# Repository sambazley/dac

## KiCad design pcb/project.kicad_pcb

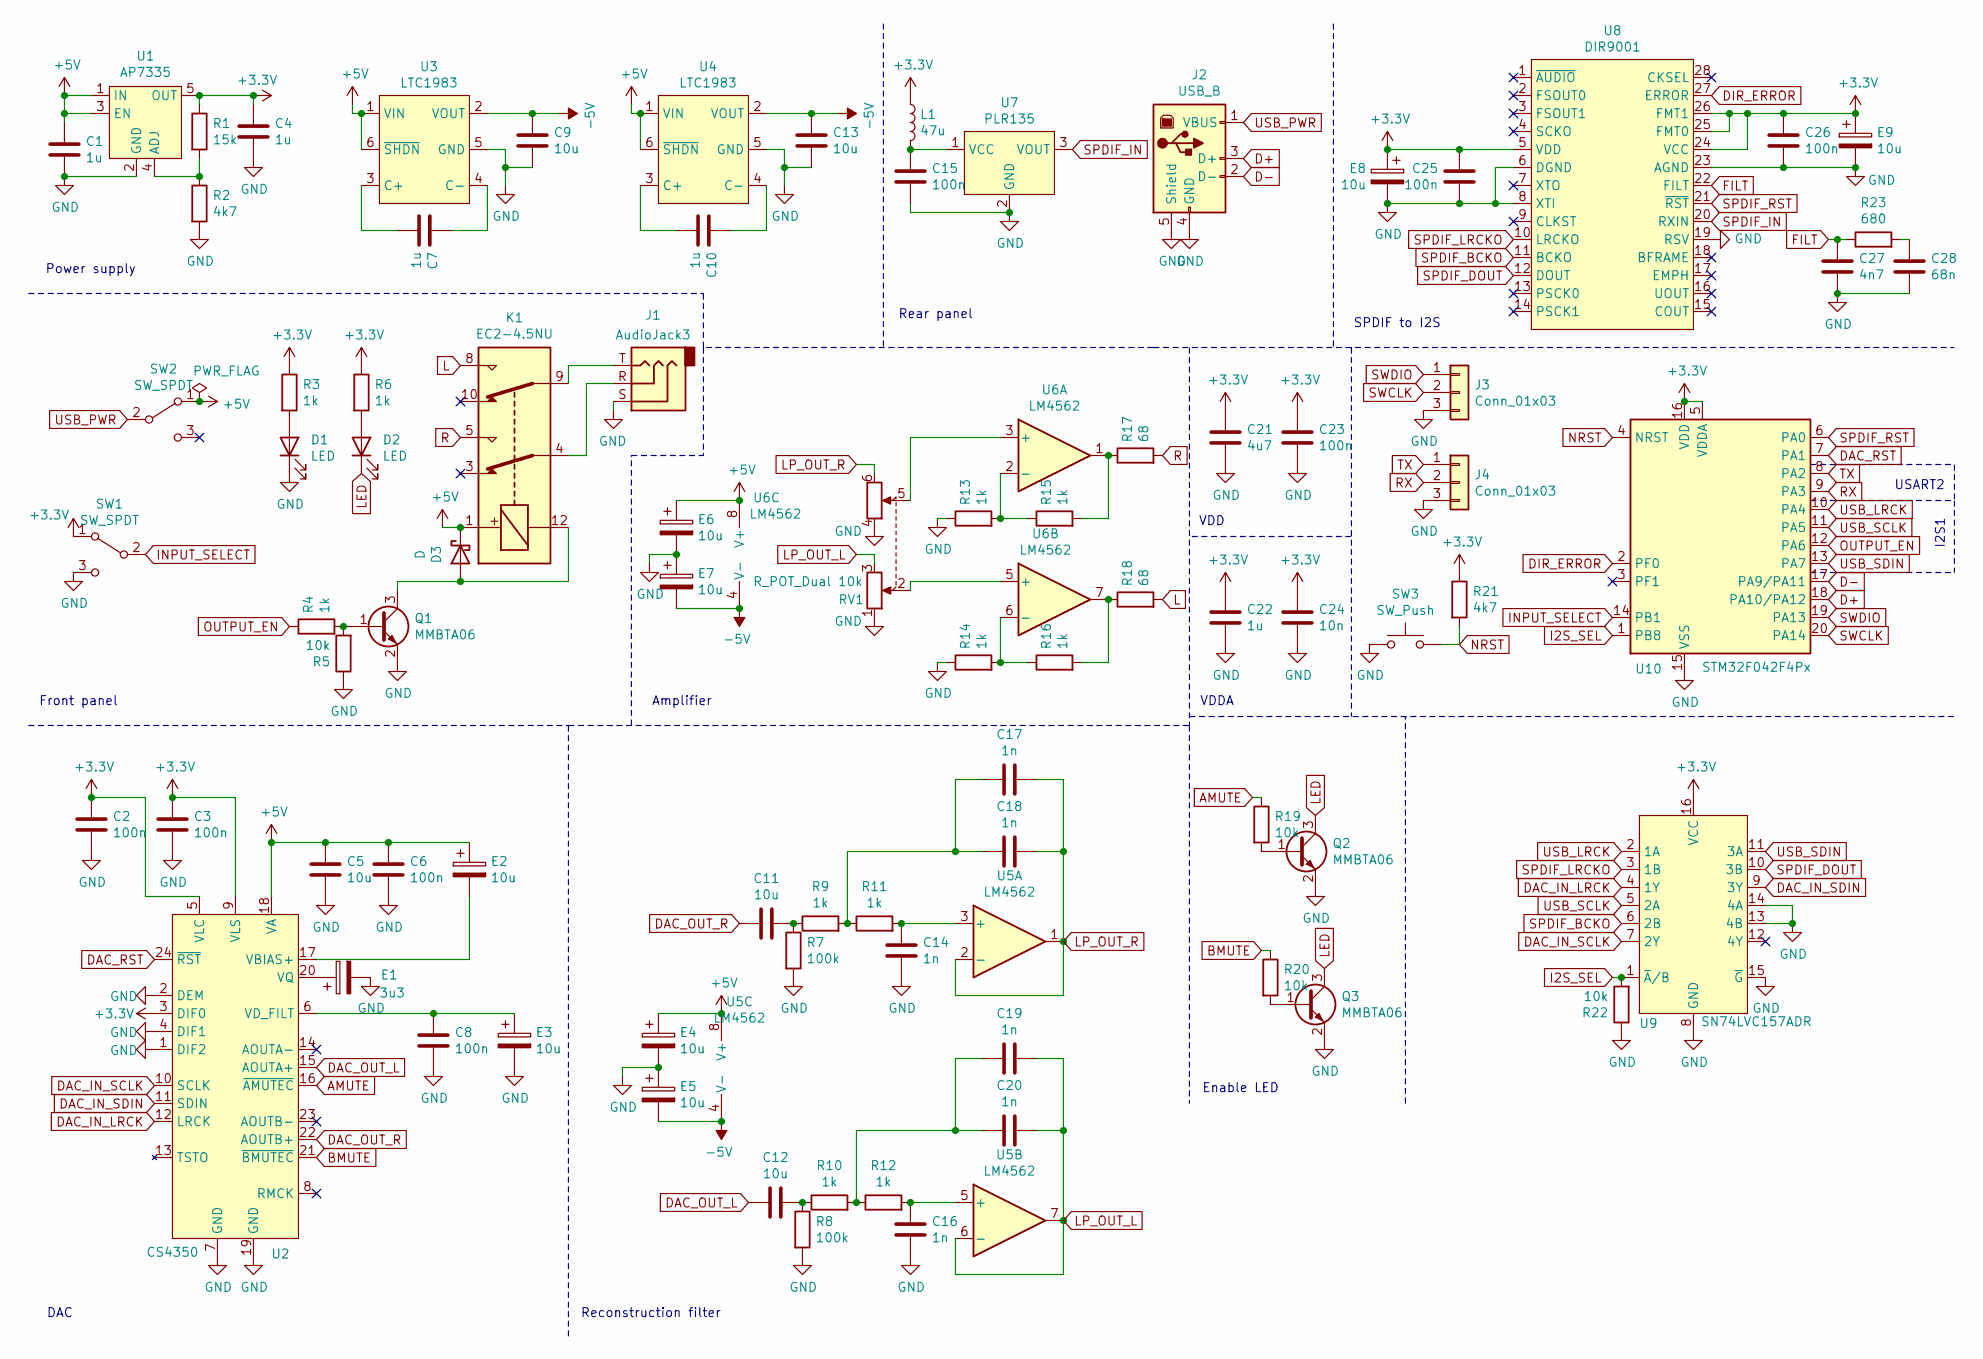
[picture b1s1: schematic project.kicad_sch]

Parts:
C1, C4, C7, C10, C22: 1u; C_0805_2012Metric
C2, C3, C6, C8, C15, C23, C25, C26: 100n; C_0805_2012Metric
C5, C9, C11, C12, C13: 10u; C_0805_2012Metric
C14, C16, C17, C18, C19, C20: 1n; C_0805_2012Metric
C21: 4u7; C_0805_2012Metric
C24: 10n; C_0805_2012Metric
C27: 4n7; C_0805_2012Metric
C28: 68n; C_0805_2012Metric
D1, D2: LED; LED_0805_2012Metric_Pad1.15x1.40mm_HandSolder
D3: D; D_SOD-523
E1: 3u3; CP_Elec_4x4.5
E2, E3, E4, E5, E6, E7, E8, E9: 10u; CP_Radial_D5.0mm_P2.00mm
J1: AudioJack3; SJ-63053A
J2: USB_B; UJ2-BH-TH
J3, J4: Conn_01x03; PinHeader_1x03_P2.54mm_Vertical
K1: EC2-4.5NU; Relay_DPDT_Kemet_EC2
L1: 47u; L_Taiyo-Yuden_NR-50xx
Q1, Q2, Q3: MMBTA06; SOT-23
R1: 15k; R_0805_2012Metric
R2, R21: 4k7; R_0805_2012Metric
R3, R4, R6, R9, R10, R11, R12, R13, R14, R15, R16: 1k; R_0805_2012Metric
R5, R19, R20, R22: 10k; R_0805_2012Metric
R7, R8: 100k; R_0805_2012Metric
R17, R18: 68; R_0805_2012Metric
R23: 680; R_0805_2012Metric
RV1: R_POT_Dual 10k; PTD902-2020K-A103
SW1, SW2: SW_SPDT; M2012SA2W40
SW3: SW_Push; SW_SPST_PTS645
U1: AP7335; SOT-23-5
U2: CS4350; TSSOP-24_4.4x7.8mm_P0.65mm
U3, U4: LTC1983; SOT-23-6
U5, U6: LM4562; DIP-8_W7.62mm_Socket
U7: PLR135
U8: DIR9001; TSSOP-28_4.4x9.7mm_P0.65mm
U9: ‎SN74LVC157ADR‎; SOIC-16_3.9x9.9mm_P1.27mm
U10: STM32F042F4Px; TSSOP-20_4.4x6.5mm_P0.65mm

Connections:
+3V3: C2.1, C3.1, C4.1, C21.1, C22.1, C23.1, C24.1, C25.1, C26.1, E8.1, E9.1, L1.1, R1.1, R3.1, R6.1, R21.1, SW1.1 (A), U1.5 (OUT), U2.3 (DIF0), U2.5 (VLC), U2.9 (VLS), U8.5 (VDD), U8.24 (VCC), U8.25 (FMT0), U8.26 (FMT1), U9.16 (VCC), U10.5 (VDDA), U10.16 (VDD)
+5V: C1.1, C5.1, C6.1, D3.1 (K), E2.1, E4.1, E6.1, K1.1, SW2.1 (A), U1.1 (IN), U1.3 (EN), U2.18 (VA), U3.1 (VIN), U3.6 (~SHDN), U4.1 (VIN), U4.6 (~SHDN), U5.8 (V+), U6.8 (V+)
-5V: C9.1, C13.1, E5.2, E7.2, U3.2 (VOUT), U4.2 (VOUT), U5.4 (V-), U6.4 (V-)
AMUTE: R19.1, U2.16 (~AMUTEC)
BMUTE: R20.1, U2.21 (~BMUTEC)
D+: J2.3 (D+), U10.18 (PA10/PA12)
D-: J2.2 (D-), U10.17 (PA9/PA11)
DAC_IN_LRCK: U2.12 (LRCK), U9.4 (1Y)
DAC_IN_SCLK: U2.10 (SCLK), U9.7 (2Y)
DAC_IN_SDIN: U2.11 (SDIN), U9.9 (3Y)
DAC_OUT_L: C12.1, U2.15 (AOUTA+)
DAC_OUT_R: C11.1, U2.22 (AOUTB+)
DAC_RST: U2.24 (~RST), U10.7 (PA1)
DIR_ERROR: U8.27 (ERROR), U10.2 (PF0)
FILT: C27.1, R23.1, U8.22 (FILT)
GND: C1.2, C2.2, C3.2, C4.2, C5.2, C6.2, C8.2, C9.2, C13.2, C14.2, C15.2, C16.2, C21.2, C22.2, C23.2, C24.2, C25.2, C26.2, C27.2, C28.2, D1.1 (K), E1.2, E3.2, E4.2, E5.1, E6.2, E7.1, E8.2, E9.2, J1.S, J2.4 (GND), J2.5 (Shield), J3.3, J4.3, Q1.2 (E), Q2.2 (E), Q3.2 (E), R2.2, R5.1, R7.2, R8.2, R13.1, R14.1, R22.1, RV1.1, RV1.4, SW1.3 (C), SW3.1, U1.2 (GND), U2.1 (DIF2), U2.2 (DEM), U2.4 (DIF1), U2.7 (GND), U2.19 (GND), U3.5 (GND), U4.5 (GND), U7.2 (GND), U8.6 (DGND), U8.8 (XTI), U8.19 (RSV), U8.23 (AGND), U9.8 (GND), U9.13 (4B), U9.14 (4A), U9.15 (~G), U10.15 (VSS)
I2S_SEL: R22.2, U9.1 (~A~/B), U10.1 (PB8)
INPUT_SELECT: SW1.2 (B), U10.14 (PB1)
L: K1.8, R18.2
LED: D2.1 (K), Q2.3 (C), Q3.3 (C)
LP_OUT_L: C19.2, C20.2, RV1.3, U5.6 (-), U5.7
LP_OUT_R: C17.2, C18.2, RV1.6, U5.1, U5.2 (-)
NRST: R21.2, SW3.2, U10.4 (NRST)
unnamed: C7.1, U3.4 (C-)
unnamed: C7.2, U3.3 (C+)
unnamed: C8.1, E3.1, U2.6 (VD_FILT)
unnamed: C10.1, U4.4 (C-)
unnamed: C10.2, U4.3 (C+)
unnamed: C11.2, R7.1, R9.1
unnamed: C12.2, R8.1, R10.1
unnamed: C14.1, R11.2, U5.3 (+)
unnamed: C15.1, L1.2, U7.1 (VCC)
unnamed: C16.1, R12.2, U5.5 (+)
unnamed: C17.1, C18.1, R9.2, R11.1
unnamed: C19.1, C20.1, R10.2, R12.1
unnamed: C28.1, R23.2
unnamed: D1.2 (A), R3.2
unnamed: D2.2 (A), R6.2
unnamed: D3.2 (A), K1.12, Q1.3 (C)
unnamed: E1.1, U2.20 (VQ)
unnamed: E2.2, U2.17 (VBIAS+)
unnamed: J1.R, K1.4
unnamed: J1.T, K1.9
unnamed: Q1.1 (B), R4.2, R5.2
unnamed: Q2.1 (B), R19.2
unnamed: Q3.1 (B), R20.2
unnamed: R1.2, R2.1, U1.4 (ADJ)
unnamed: R13.2, R15.1, U6.2 (-)
unnamed: R14.2, R16.1, U6.6 (-)
unnamed: R15.2, R17.1, U6.1
unnamed: R16.2, R18.1, U6.7
unnamed: RV1.2, U6.5 (+)
unnamed: RV1.5, U6.3 (+)
OUTPUT_EN: R4.1, U10.12 (PA6)
R: K1.5, R17.2
RX: J4.2, U10.9 (PA3)
SPDIF_BCKO: U8.11 (BCKO), U9.6 (2B)
SPDIF_DOUT: U8.12 (DOUT), U9.10 (3B)
SPDIF_IN: U7.3 (VOUT), U8.20 (RXIN)
SPDIF_LRCKO: U8.10 (LRCKO), U9.3 (1B)
SPDIF_RST: U8.21 (~RST), U10.6 (PA0)
SWCLK: J3.2, U10.20 (PA14)
SWDIO: J3.1, U10.19 (PA13)
TX: J4.1, U10.8 (PA2)
USB_LRCK: U9.2 (1A), U10.10 (PA4)
USB_PWR: J2.1 (VBUS), SW2.2 (B)
USB_SCLK: U9.5 (2A), U10.11 (PA5)
USB_SDIN: U9.11 (3A), U10.13 (PA7)

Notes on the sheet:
DAC
Front panel
Power supply
Amplifier
Reconstruction filter
Rear panel
VDD
VDDA
Enable LED
SPDIF to I2S
USART2
I2S1

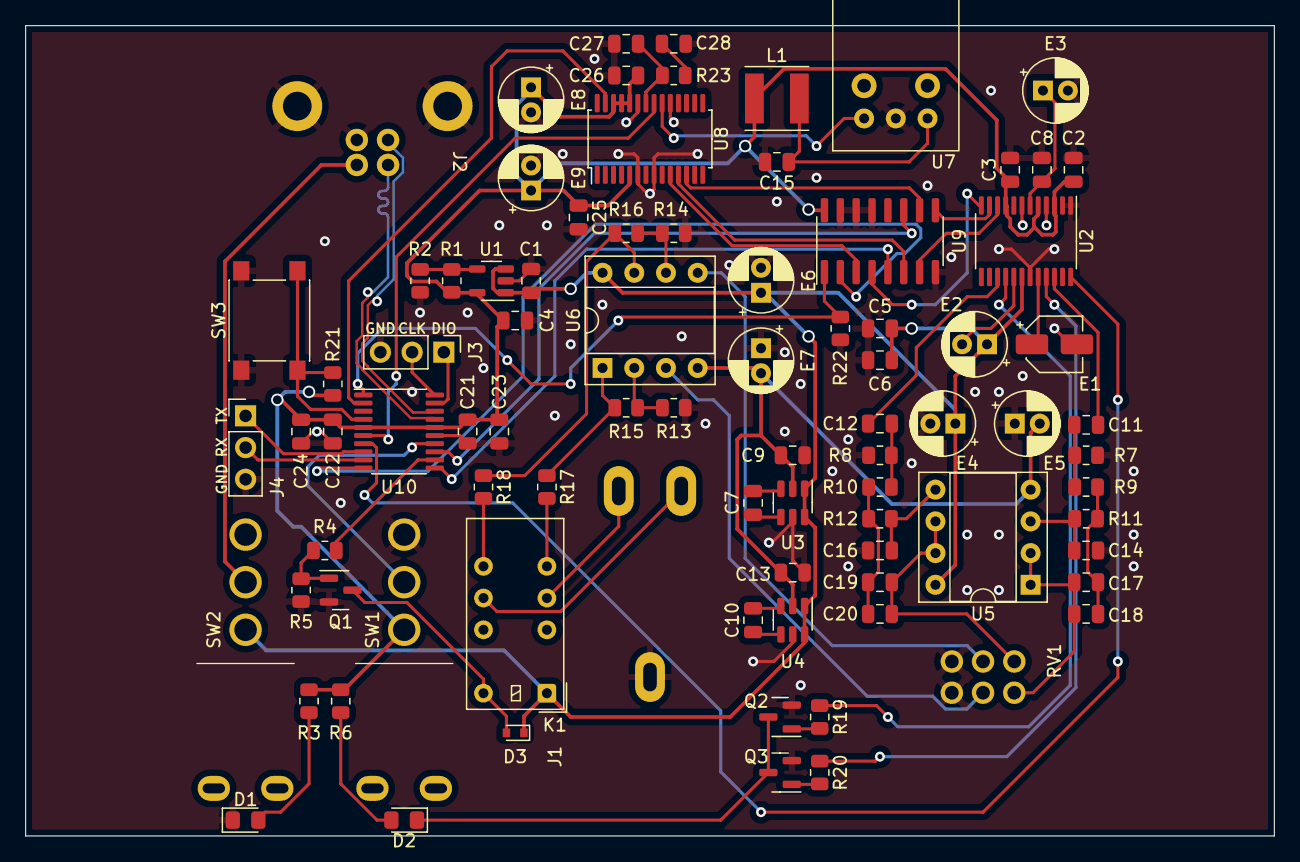
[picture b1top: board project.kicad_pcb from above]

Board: 2 copper layers, 100.0 x 64.9 mm, 86 parts (0 on the bottom side), 68 nets.

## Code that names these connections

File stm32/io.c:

/* Copyright (C) 2021 Sam Bazley
 *
 * This software is provided 'as-is', without any express or implied
 * warranty.  In no event will the authors be held liable for any damages
 * arising from the use of this software.
 *
 * Permission is granted to anyone to use this software for any purpose,
 * including commercial applications, and to alter it and redistribute it
 * freely, subject to the following restrictions:
 *
 * 1. The origin of this software must not be misrepresented; you must not
 *    claim that you wrote the original software. If you use this software
 *    in a product, an acknowledgment in the product documentation would be
 *    appreciated but is not required.
 * 2. Altered source versions must be plainly marked as such, and must not be
 *    misrepresented as being the original software.
 * 3. This notice may not be removed or altered from any source distribution.
 */

#include "io.h"
#include "dac.h"
#include "spdif.h"
#include "uart.h"
#include "usb.h"
#include <stm32f0xx.h>

/* GPIOA */
#define OUTPUT_EN 6
#define I2S_SEL 8
#define INPUT_SEL 1

/* GPIOF */
#define DIR_ERROR 0

static void input_select_setup()
{
	RCC->AHBENR |= RCC_AHBENR_GPIOBEN;

	GPIOB->MODER &= ~(3 << (2 * I2S_SEL));
	GPIOB->MODER |= 1 << (2 * 8);

	GPIOB->MODER &= ~(3 << (2 * INPUT_SEL));
}

void io_enable()
{
	RCC->AHBENR |= RCC_AHBENR_GPIOAEN;
	RCC->AHBENR |= RCC_AHBENR_GPIOFEN;

	GPIOA->MODER &= ~(3 << (2 * OUTPUT_EN));
	GPIOA->MODER |= 1 << (2 * OUTPUT_EN);

	GPIOF->MODER &= ~(3 << (2 * DIR_ERROR));

	input_select_setup();

	spdif_en(1);
	dac_en(1);

	for (int i = 0; i < 10000000; i++) {
		__NOP();
	}

	GPIOA->ODR |= 1 << OUTPUT_EN;

	while (1) {
		if (GPIOB->IDR & (1 << INPUT_SEL)) {
			GPIOB->ODR &= ~(1 << I2S_SEL);
			usb_audio_en(1);
		} else {
			if (GPIOF->IDR & (1 << DIR_ERROR)) {
				GPIOB->ODR &= ~(1 << I2S_SEL);
				usb_audio_en(0);
			} else {
				GPIOB->ODR |= 1 << I2S_SEL;
			}
		}
	}
}

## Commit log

2021-04-12 Add PCB files
2021-04-12 Add README
2021-04-14 Work around for whistle when SPDIF is stopped
    Switch DAC I2S source to USB and clear USB audio buffer to prevent
    whistling sound when SPDIF stops or is unplugged.
2021-07-11 Use libstm32usb
2025-06-17 Fix USB buffer collision by adjusting HSI48 with CSR
2025-06-17 Update libstm32usb
2026-05-17 Fix linker warnings
2026-05-17 Add DFU support
